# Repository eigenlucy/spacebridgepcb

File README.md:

# spacebridgepcb

spacebridge pcb, v2

Created by lucy moglia <eigenlucy@proton.me>

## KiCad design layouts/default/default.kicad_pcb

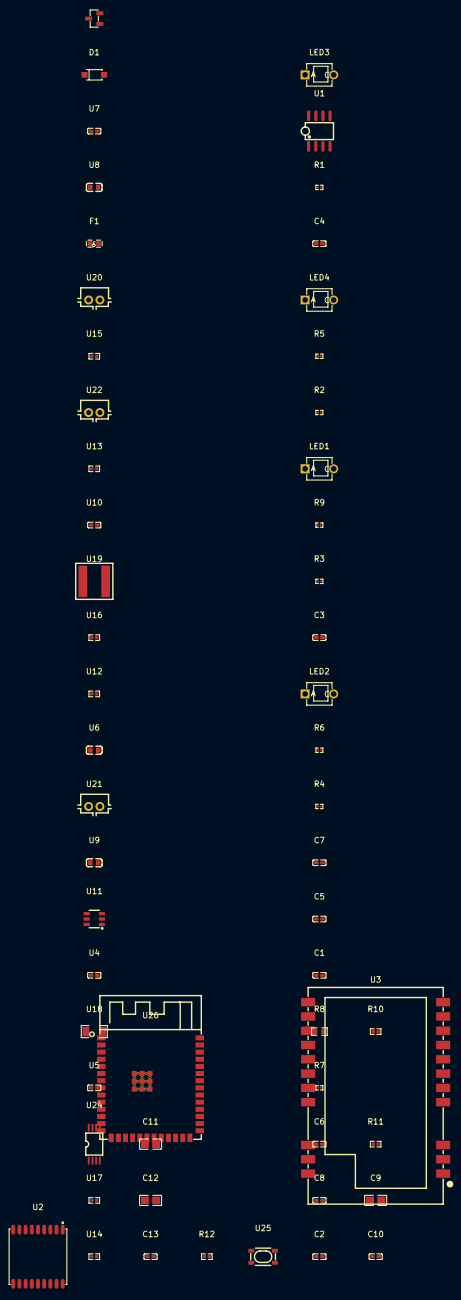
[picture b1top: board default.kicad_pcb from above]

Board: 2 copper layers, 57 parts (0 on the bottom side), 34 nets, no tracks yet.

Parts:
C1, C2, C3, C4, C5, C6, C7, C8, C10, C13: 100nF ±10% 16V X7R; C0402-b3ef17
C9: 100nF ±10% 50V X7R; C0805-3b2e55
C11, C12: 10µF ±10% 25V X5R; C0805-3b2e55
D1: SOD-123F_L2.7-W1.6-LS3.8-RD-1-139753
F1: F0603-5fdc66
LED1, LED2, LED3, LED4: SENSOR-TH_BPW34-c0a4b0
R1, R2, R3, R4, R5, R6, R7, R9: 0Ω 50mW; R0201-27027e
R8: 10kΩ ±1% 100mW; R0603-ebcab9
R10, R11: 1kΩ ±1% 62.5mW; R0402-56259e
R12: 10kΩ ±1% 62.5mW; R0402-56259e
U1: SOIC-8_L5.0-W4.0-P1.27-LS6.0-BL-294f77
U2: GPSM-SMD_ATGM336H-TR-d79f58
U3: WIRELM-SMD_E22-900M30S-98c301
U4, U7: 100nF ±10% 16V X7R; C0402-b3ef17
U5: 1µF ±10% 25V X5R; C0402-b3ef17
U6, U9: 10µF ±10% 10V X5R; C0603-bd72f6
U8: 4.7µF ±10% 10V X5R; C0603-bd72f6
U10: 1nF ±20% 50V X7R; C0402-b3ef17
U11: SOT-23-6_L2.9-W1.6-P0.95-LS2.8-BR
U12: 1MΩ ±1% 62.5mW; R0402-56259e
U13: 450kΩ ±1% 62.5mW; R0402-56259e
U14, U16, U17: 1kΩ ±1% 62.5mW; R0402-56259e
U15: 100Ω ±1% 62.5mW; R0402-56259e
U18: 10mΩ ±1% 1W; R1206-bdb864
U19: IND-SMD_L6.6-W6.4
U20, U21, U22: CONN-TH_B2B-PH-K-S
U23: SOT-23-3_L2.9-W1.3-P1.90-LS2.4-BR-688f29
U24: TSSOP-8_L4.4-W3.0-P0.65-LS6.4-BL
U25: KEY-SMD_4P-L4.2-W3.2-P2.20-LS4.6
U26: WIRELM-SMD_ESP32-S3-WROOM-1

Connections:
A: D1.2, U21.2
ICTRL_MINUS: U5.2, U17.1, U24.6
ICTRL_PLUS: U5.1, U16.1, U24.7
IN1plus: R1.2, R2.1, U1.3
IN2minus: C5.1, R4.2, R5.1, U1.6
IN2plus: C6.1, R6.2, R7.1, U1.5
K: C1.1, LED1.2, LED2.2, LED3.2, LED4.2, R3.1, U1.2
LX: U19.2, U24.3
OUT1: C1.2, C3.1, R3.2, U1.1
OUT2: C5.2, R5.2, R8.1, U1.7
RXEN: R10.2, U3.6
Reserved: U2.15, U2.18
TXEN: R11.2, U3.7
VCC: U2.8, U2.14
VCTRL: U10.1, U12.2, U13.1, U24.5
VDD: U4.1, U15.1, U23.2
VOUT: U8.1, U16.2, U18.1, U24.4
XSHUT: U7.1, U14.2, U24.1, U24.8
detector-net: C3.2, R4.1
gnd: C9.2, C10.2, U3.1, U3.2, U3.3, U3.4, U3.5, U3.11, U3.12, U3.20, U3.22
gnd-1: C2.2, C4.2, C6.2, C7.2, LED1.1, LED2.1, LED3.1, LED4.1, R2.2, R7.2, R9.2, U1.4
gnd-2: U6.2, U7.2, U8.2, U9.2, U10.2, U13.2, U22.2, U23.1, U24.2
gnd-3: C11.2, C12.2, C13.2, U25.3, U25.4, U26.1, U26.40, U26.41
gps-gnd: U2.1, U2.10, U2.12
hv: F1.1, U9.1, U12.1, U15.2, U17.2, U18.2, U20.1
hv-1: C2.1, C4.1, R1.1, R6.1, U1.8
hv-2: C9.1, C10.1, R10.1, R11.1, U3.9, U3.10
hv-3: C11.1, C12.1, C13.1, R12.1, U26.2
in: R12.2, U25.1, U25.2
mppt-gnd: D1.1, U4.2, U20.2, U23.3
mppt-hv: U6.1, U14.1, U19.1, U22.1
out: C8.2, R9.1
p2: F1.2, U21.1
unnamed[0]: C7.1, C8.1, R8.2

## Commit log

2025-04-30 built
